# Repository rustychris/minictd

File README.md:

# minictd
Hardware and firmware for miniature, low-fi CTD

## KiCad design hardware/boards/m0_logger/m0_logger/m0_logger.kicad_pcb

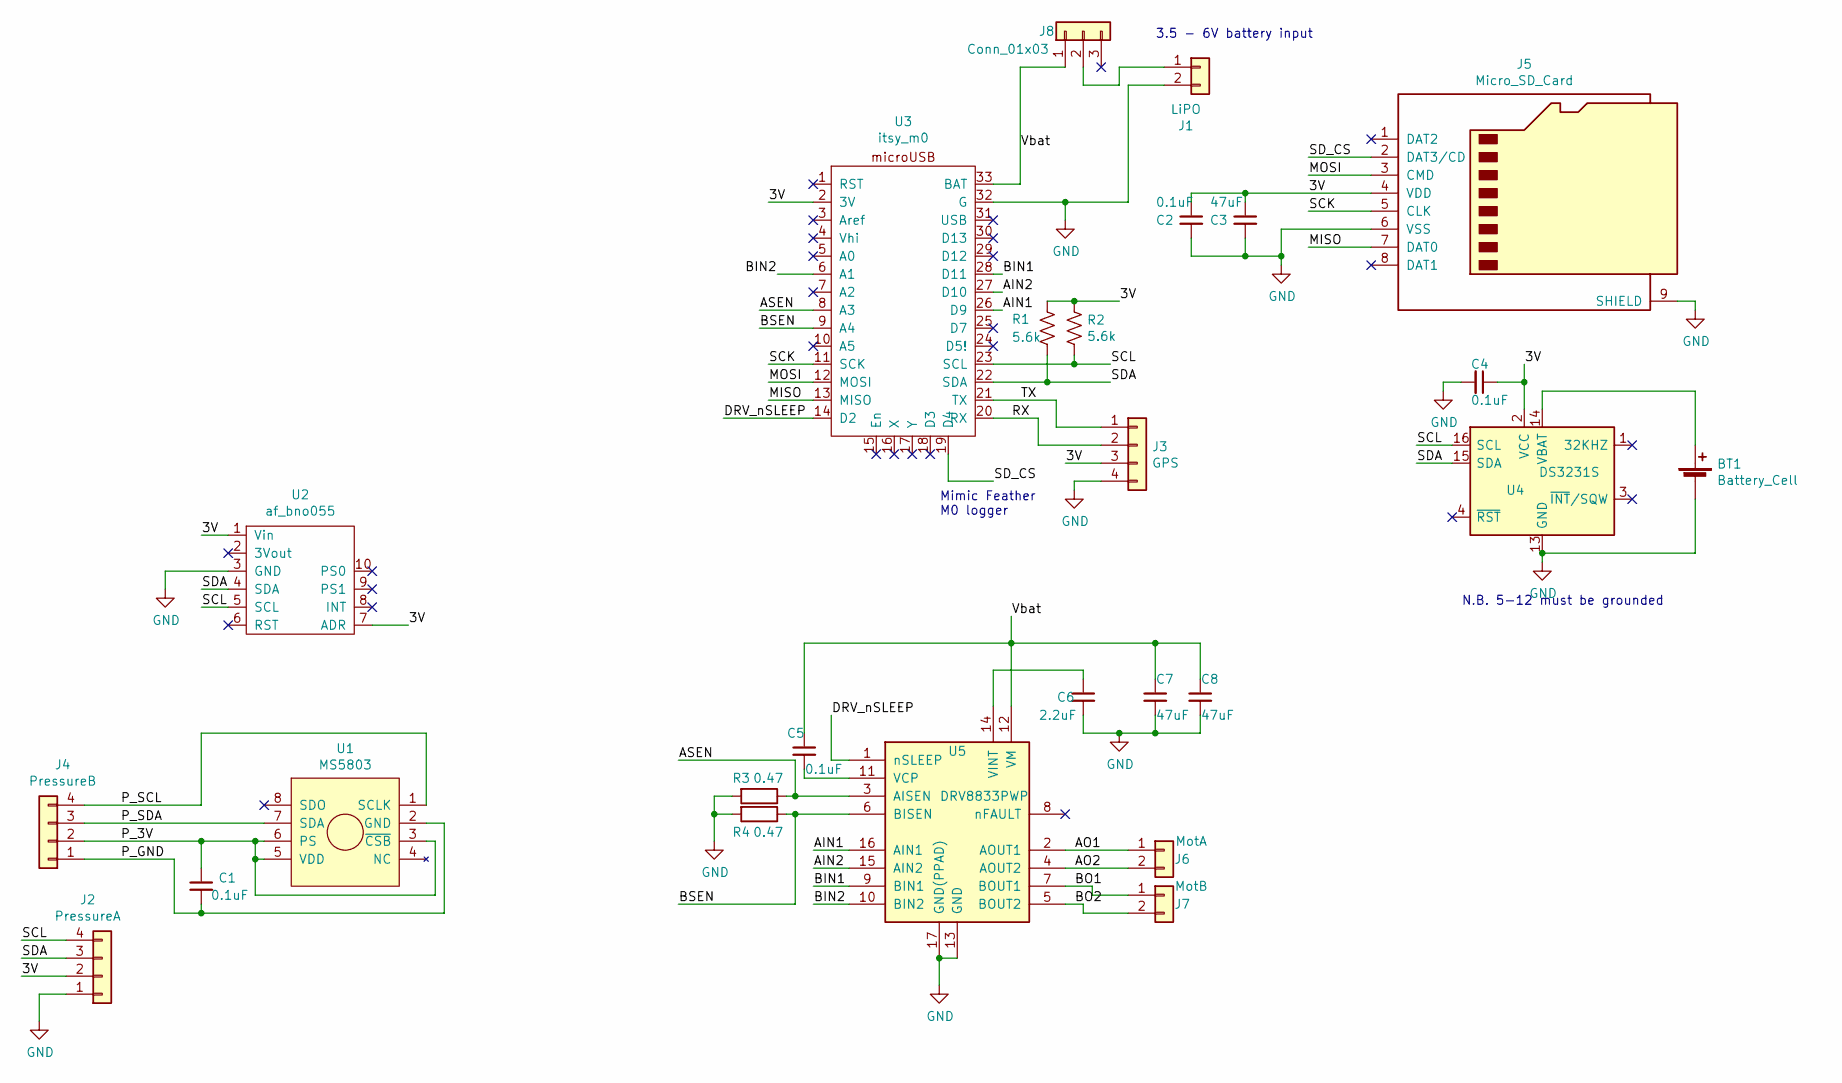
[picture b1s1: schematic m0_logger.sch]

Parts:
BT1: Battery_Cell; BatteryHolder_Keystone_500
C1, C2, C4, C5: 0.1uF; C_0805_2012Metric_Pad1.15x1.40mm_HandSolder
C3, C7, C8: 47uF; C_0805_2012Metric_Pad1.15x1.40mm_HandSolder
C6: 2.2uF; C_0805_2012Metric_Pad1.15x1.40mm_HandSolder
J1: LiPO; JST_PH_S2B-PH-K_1x02_P2.00mm_Horizontal
J2: PressureA; Molex_PicoBlade_53047-0810_1x04_P1.25mm_Vertical
J3: GPS; Molex_PicoBlade_53047-0810_1x04_P1.25mm_Vertical
J4: PressureB; PinHeader_1x04_P2.54mm_Vertical
J5: Micro_SD_Card; microSD_HC_Hirose_DM3AT-SF-PEJM5
J6: MotA; Molex_PicoBlade_53047-0410_1x02_P1.25mm_Vertical
J7: MotB; Molex_PicoBlade_53047-0410_1x02_P1.25mm_Vertical
J8: Conn_01x03; PinHeader_1x03_P2.54mm_Vertical
R1, R2: 5.6k; R_0805_2012Metric_Pad1.15x1.40mm_HandSolder
R3, R4: 0.47; R_0805_2012Metric_Pad1.15x1.40mm_HandSolder
U1: MS5803; ms5803_rh
U2: af_bno055; afBNO055
U3: itsy_m0; ItsyBitsyM0
U4: DS3231S; SOIC-16W_7.5x10.3mm_P1.27mm
U5: DRV8833PWP; HTSSOP-16-1EP_4.4x5mm_P0.65mm_EP3.4x5mm_Mask2.46x2.31mm_The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

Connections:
/3V: C2.1, C3.1, C4.1, J2.2, J3.3, J5.4 (VDD), R1.1, R2.1, U2.1 (Vin), U2.7 (ADR), U3.2 (3V), U4.2 (VCC)
/AIN1: U3.26 (D9), U5.16 (AIN1)
/AIN2: U3.27 (D10), U5.15 (AIN2)
/AO1: J6.1, U5.2 (AOUT1)
/AO2: J6.2, U5.4 (AOUT2)
/ASEN: R3.1, U3.8 (A3), U5.3 (AISEN)
/BIN1: U3.28 (D11), U5.9 (BIN1)
/BIN2: U3.6 (A1), U5.10 (BIN2)
/BO1: J7.1, U5.7 (BOUT1)
/BO2: J7.2, U5.5 (BOUT2)
/BSEN: R4.1, U3.9 (A4), U5.6 (BISEN)
/DRV_nSLEEP: U3.14 (D2), U5.1 (nSLEEP)
/MISO: J5.7 (DAT0), U3.13 (MISO)
/MOSI: J5.3 (CMD), U3.12 (MOSI)
/P_3V: C1.1, J4.2, U1.3 (~CSB~), U1.5 (VDD), U1.6 (PS); also elsewhere on the board
/P_GND: C1.2, J4.1, U1.2 (GND); also elsewhere on the board
/P_SCL: J4.4, U1.1 (SCLK); also elsewhere on the board
/P_SDA: J4.3, U1.7 (SDA); also elsewhere on the board
/RX: J3.2, U3.20 (RX)
/SCK: J5.5 (CLK), U3.11 (SCK)
/SCL: J2.4, R2.2, U2.5 (SCL), U3.23 (SCL), U4.16 (SCL)
/SDA: J2.3, R1.2, U2.4 (SDA), U3.22 (SDA), U4.15 (SDA)
/SD_CS: J5.2 (DAT3/CD), U3.19 (D4)
/TX: J3.1, U3.21 (TX)
/Vbat: C5.1, C7.1, C8.1, J8.1, U3.33 (BAT), U5.12 (VM)
GND: BT1.2 (-), C2.2, C3.2, C4.2, C6.2, C7.2, C8.2, J1.2, J2.1, J3.4, J5.6 (VSS), J5.9 (SHIELD), R3.2, R4.2, U2.3 (GND), U3.32 (G), U4.5 (GND), U4.6 (GND), U4.7 (GND), U4.8 (GND), U4.9 (GND), U4.10 (GND), U4.11 (GND), U4.12 (GND), U4.13 (GND), U5.13 (GND), U5.17 (GND(PPAD))
unnamed: BT1.1 (+), U4.14 (VBAT)
unnamed: C5.2, U5.11 (VCP)
unnamed: C6.1, U5.14 (VINT)
unnamed: J1.1, J8.2

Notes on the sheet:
N.B. 5-12 must be grounded
Mimic Feather M0 logger
3.5 - 6V battery input

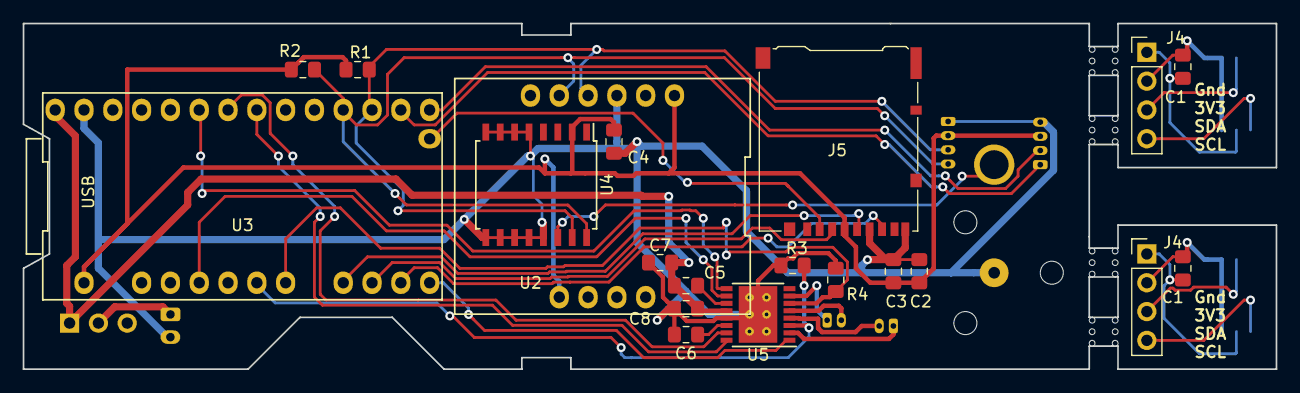
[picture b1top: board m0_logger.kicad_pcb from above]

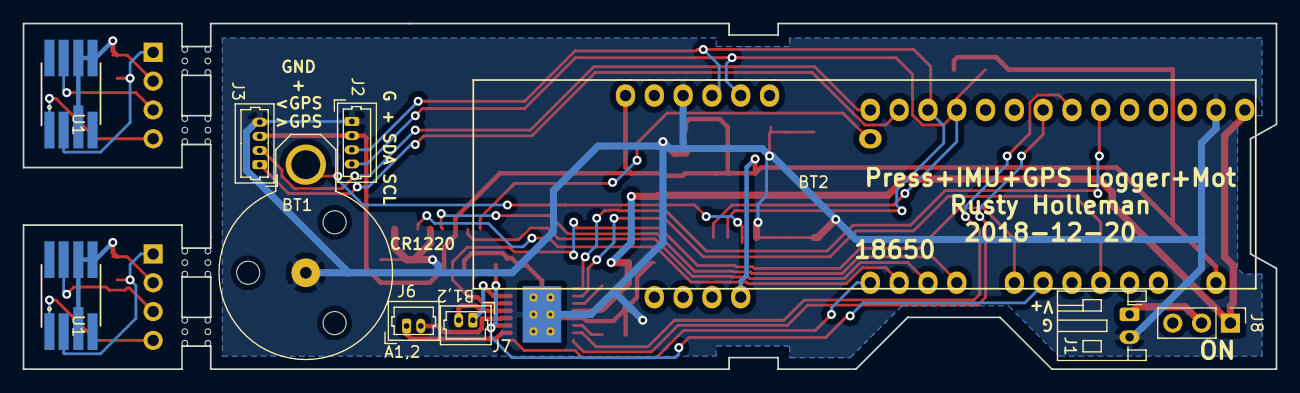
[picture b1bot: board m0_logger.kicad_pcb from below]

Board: 2 copper layers, 110.5 x 30.5 mm, 30 parts (10 on the bottom side), 30 nets.

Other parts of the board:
BT2: 18650, protected; af18650_outline
C1#2: 0.1uF; C_0805_2012Metric_Pad1.15x1.40mm_HandSolder
J4#2: PressureB; PinHeader_1x04_P2.54mm_Vertical
U1#2: MS5803; ms5803_rh

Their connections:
/P_3V: C1#2.1, J4#2.2, U1#2.3, U1#2.5, U1#2.6; also elsewhere on the board
/P_GND: C1#2.2, J4#2.1, U1#2.2; also elsewhere on the board
/P_SCL: J4#2.4, U1#2.1; also elsewhere on the board
/P_SDA: J4#2.3, U1#2.7; also elsewhere on the board

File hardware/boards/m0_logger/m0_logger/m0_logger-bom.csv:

"Ref","Qnty","Value","Cmp name","Footprint","Description","Vendor"
"BT1, ","1","Battery_Cell","Battery_Cell","Battery:BatteryHolder_Keystone_500","Single-cell battery","36-500-ND"
"C1, C4, C2, ","3","0.1uF","C_Small","Capacitor_SMD:C_0805_2012Metric_Pad1.15x1.40mm_HandSolder","Unpolarized capacitor, small symbol","478-1395-1-ND"
"C3, ","1","47uF","C_Small","Capacitor_SMD:C_0805_2012Metric_Pad1.15x1.40mm_HandSolder","Unpolarized capacitor, small symbol","490-9961-1-ND"
"J1, ","1","LiPO","Conn_01x02","Connector_JST:JST_PH_S2B-PH-K_1x02_P2.00mm_Horizontal","Generic connector, single row, 01x02, script generated (kicad-library-utils/schlib/autogen/connector/)","455-1719-ND"
"J2, ","1","PressureA","Conn_01x04","Connector_PinHeader_2.54mm:PinHeader_2x02_P2.54mm_Horizontal","Generic connector, single row, 01x04, script generated (kicad-library-utils/schlib/autogen/connector/)","609-3333-ND"
"J3, ","1","GPS","Conn_01x04","Connector_PinHeader_2.54mm:PinHeader_2x02_P2.54mm_Horizontal","Generic connector, single row, 01x04, script generated (kicad-library-utils/schlib/autogen/connector/)","609-3333-ND"
"J4, ","1","PressureB","Conn_01x04","Connector_PinHeader_2.54mm:PinHeader_1x04_P2.54mm_Vertical","Generic connector, single row, 01x04, script generated (kicad-library-utils/schlib/autogen/connector/)","609-3255-ND"
"J5, ","1","Micro_SD_Card","Micro_SD_Card","Connector_Card:microSD_HC_Hirose_DM3AT-SF-PEJM5","Micro SD Card Socket","HR1964CT-ND"
"R2, R1, ","2","5.6k","R_US","Resistor_SMD:R_0805_2012Metric_Pad1.15x1.40mm_HandSolder","Resistor, US symbol","A126380CT-ND"
"U1, ","1","MS5803","MS5803","m0_logger_footprints:ms5803_rh","","223-1625-5-ND"
"U2, ","1","af_bno055","af_bno055","m0_logger_footprints:afBNO055","","1528-1426-ND"
"U3, ","1","itsy_m0","itsy_m0","m0_logger_footprints:ItsyBitsyM0","","1528-2554-ND"
"U4, ","1","DS3231S","DS3231M","Package_SO:SOIC-16W_7.5x10.3mm_P1.27mm","Extremely Accurate I2C-Integrated RTC/TCXO/Crystal SOIC-16","DS3231S#-ND"

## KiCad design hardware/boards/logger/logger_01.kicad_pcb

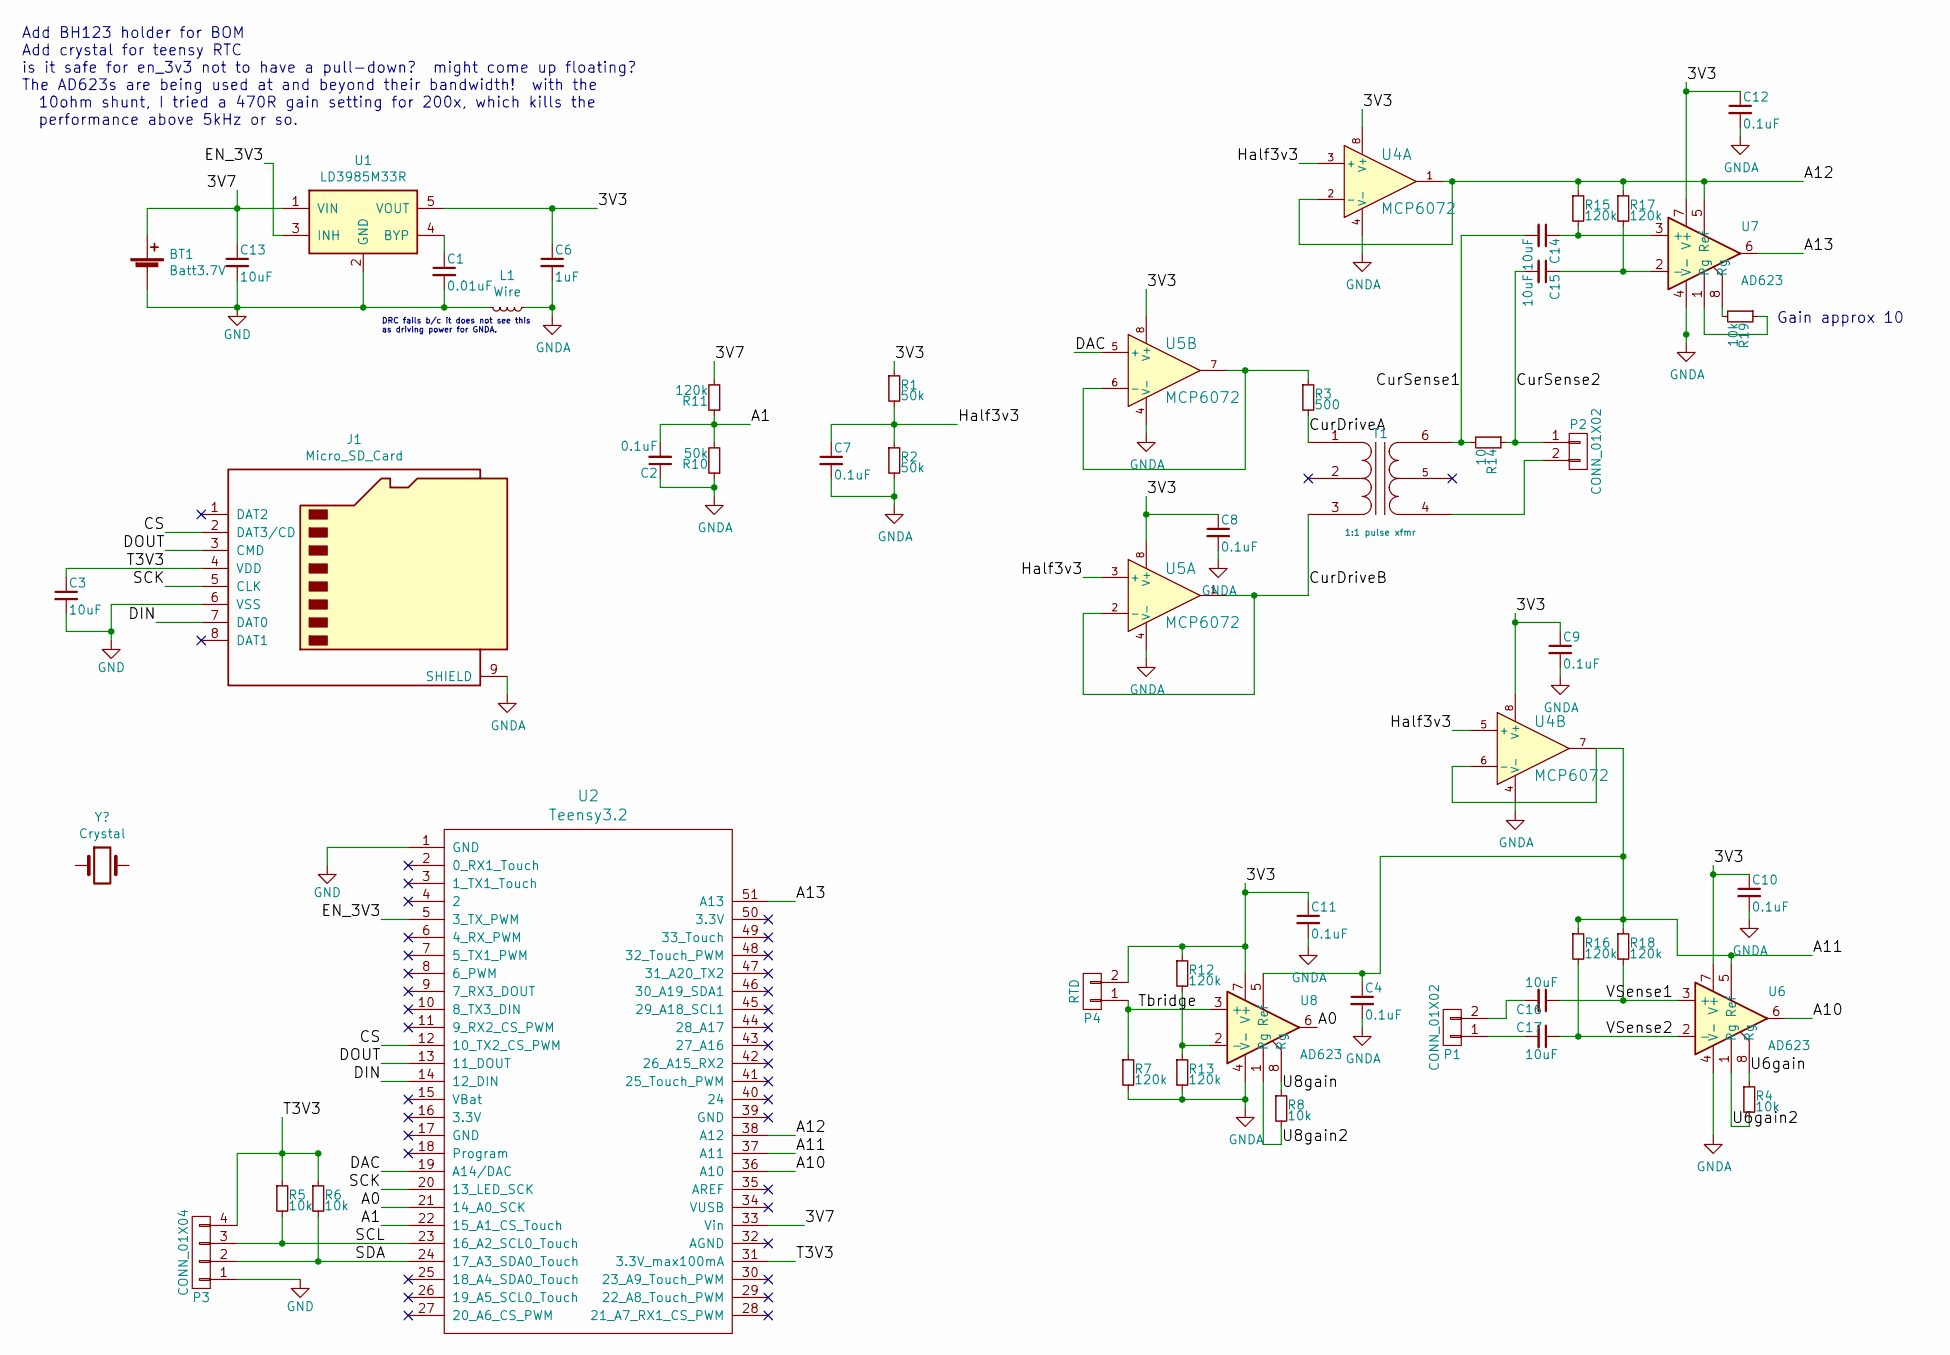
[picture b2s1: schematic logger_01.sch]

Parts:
BT1: Batt3.7V; Pin_Header_Straight_1x02_Pitch2.54mm
C1: 0.01uF; C_0805_HandSoldering; part_num CC0805KRX7R9BB103; digikey_num 311-1136-1-ND
C2, C7: 0.1uF; C_0805_HandSoldering; part_num 08055C104KAT2A; digikey_num 478-1395-1-ND
C3, C13, C14, C15, C16, C17: 10uF; C_0805_HandSoldering; part_num GRM21BR61E106KA73L; digikey_num 490-5523-1-ND
C4, C8, C9, C10, C11, C12: 0.1uF; C_0805_HandSoldering; part_num 08055C104KAT2A
C6: 1uF; C_0805_HandSoldering; part_num GRM21BR61E106KA73L; digikey_num 490-5523-1-ND
J1: Micro_SD_Card; molex5031821852; part_num 5031821852; digikey_num WM12834CT-ND
L1: Wire; R_0805
P1, P2: CONN_01X02; Pin_Header_Straight_1x02_Pitch2.54mm
P3: CONN_01X04; Pin_Header_Straight_1x04_Pitch2.54mm; part_num S1011EC-12-ND; digikey_num PRPC012SAAN-RC
P4: RTD; Pin_Header_Straight_1x02_Pitch2.54mm
R1, R2, R10: 50k; R_0805_HandSoldering; part_num RT0805DRE0722K1L; digikey_num 311-2825-1-ND
R3: 500; R_0805_HandSoldering; part_num RR1220P-471-D; digikey_num RR12P470DCT-ND
R4, R6, R8, R19: 10k; R_0805_HandSoldering; part_num RT0805DRD0712K1L
R5: 10k; R_0805_HandSoldering; part_num RT0805DRD0712K1L; digikey_num 311-2703-1-ND
R7, R12, R13, R15, R16, R17, R18: 120k; R_0805_HandSoldering; part_num RT0805DRD07120KL; digikey_num 311-2702-1-ND
R11: 120k; R_0805_HandSoldering; part_num RT0805DRE0722K1L; digikey_num 311-2825-1-ND
R14: 10; R_0805_HandSoldering; part_num RT0805DRD0710RL; digikey_num 311-2700-1-ND
T1: 1:1 pulse xfmr; 6pin_pulse_transformer; part_num 78253/55JC; digikey_num 811-2415-ND
U1: LD3985M33R; SOT-23-5; part_num LD3985M33R; digikey_num 497-3504-1-ND
U2: Teensy3.2; Teensy32_for_logger
U4: MCP6072; SOIC-8_3.9x4.9mm_Pitch1.27mm; part_num MCP6072-E/SN; digikey MCP6072-E/SN-ND
U5: MCP6072; SOIC-8_3.9x4.9mm_Pitch1.27mm; part_num MCP6072-E/SN; digikey_num MCP6072-E/SN-ND
U6, U7, U8: AD623; SOIC-8_3.9x4.9mm_Pitch1.27mm; part_num AD623ARZ; digikey_num AD623ARZ-ND

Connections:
/3V3: C6.1, C8.1, C9.1, C10.1, C11.1, C12.1, P4.2, R1.1, R12.1, U1.5 (VOUT), U4.8 (V+), U5.8 (V+), U6.7 (V+), U7.7 (V+), U8.7 (V+)
/3V7: BT1.1 (+), C13.1, R11.2, U1.1 (VIN), U2.33 (Vin)
/A0: U2.21 (14_A0_SCK), U8.6
/A1: C2.2, R10.2, R11.1, U2.22 (15_A1_CS_Touch)
/A10: U2.36 (A10), U6.6
/A11: C4.1, R16.1, R18.1, U2.37 (A11), U4.6 (-), U4.7, U6.5 (Ref), U8.5 (Ref)
/A12: R15.1, R17.1, U2.38 (A12), U4.1, U4.2 (-), U7.5 (Ref)
/A13: U2.51 (A13), U7.6
/CS: J1.2 (DAT3/CD), U2.12 (10_TX2_CS_PWM)
/CurDriveA: R3.2, T1.1 (PR1)
/CurDriveB: T1.3 (PR2), U5.1, U5.2 (-)
/CurSense1: C14.2, R14.2, T1.6 (S2)
/CurSense2: C15.2, P2.1, R14.1
/DAC: U2.19 (A14/DAC), U5.5 (+)
/DIN: J1.7 (DAT0), U2.14 (12_DIN)
/DOUT: J1.3 (CMD), U2.13 (11_DOUT)
/EN_3V3: U1.3 (INH), U2.5 (3_TX_PWM)
/Half3v3: C7.1, R1.2, R2.1, U4.3 (+), U4.5 (+), U5.3 (+)
/SCK: J1.5 (CLK), U2.20 (13_LED_SCK)
/SCL: P3.3, R5.2, U2.23 (16_A2_SCL0_Touch)
/SDA: P3.2, R6.2, U2.24 (17_A3_SDA0_Touch)
/T3V3: C3.1, J1.4 (VDD), P3.4, R5.1, R6.1, U2.31 (3.3V_max100mA)
/Tbridge: P4.1, R7.1, U8.3 (+)
/U6gain: R4.1, U6.8 (Rg)
/U6gain2: R4.2, U6.1 (Rg)
/U8gain: R8.1, U8.8 (Rg)
/U8gain2: R8.2, U8.1 (Rg)
/VSense1: C16.1, R18.2, U6.3 (+)
/VSense2: C17.1, R16.2, U6.2 (-)
GND: BT1.2 (-), C1.2, C3.2, C13.2, J1.6 (VSS), L1.2, P3.1, U1.2 (GND), U2.1 (GND); also elsewhere on the board
GNDA: C2.1, C4.2, C6.2, C7.2, C8.2, C9.2, C10.2, C11.2, C12.2, J1.9 (SHIELD), L1.1, R2.2, R7.2, R10.1, R13.2, U4.4 (V-), U5.4 (V-), U6.4 (V-), U7.4 (V-), U8.4 (V-); also elsewhere on the board
unnamed: C1.1, U1.4 (BYP)
unnamed: C14.1, R15.2, U7.3 (+)
unnamed: C15.1, R17.2, U7.2 (-)
unnamed: C16.2, P1.2
unnamed: C17.2, P1.1
unnamed: P2.2, T1.4 (S1)
unnamed: R3.1, U5.6 (-), U5.7
unnamed: R12.2, R13.1, U8.2 (-)
unnamed: R19.1, U7.1 (Rg)
unnamed: R19.2, U7.8 (Rg)

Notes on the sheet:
Gain approx 10
DRC fails b/c it does not see this as driving power for GNDA.
Add BH123 holder for BOM Add crystal for teensy RTC is it safe for en_3v3 not to have a pull-down? might come up floating? The AD623s are being used at and beyond their bandwidth! with the 10ohm shunt, I tried a 470R gain setting for 200x, which kills the performance above 5kHz or so.

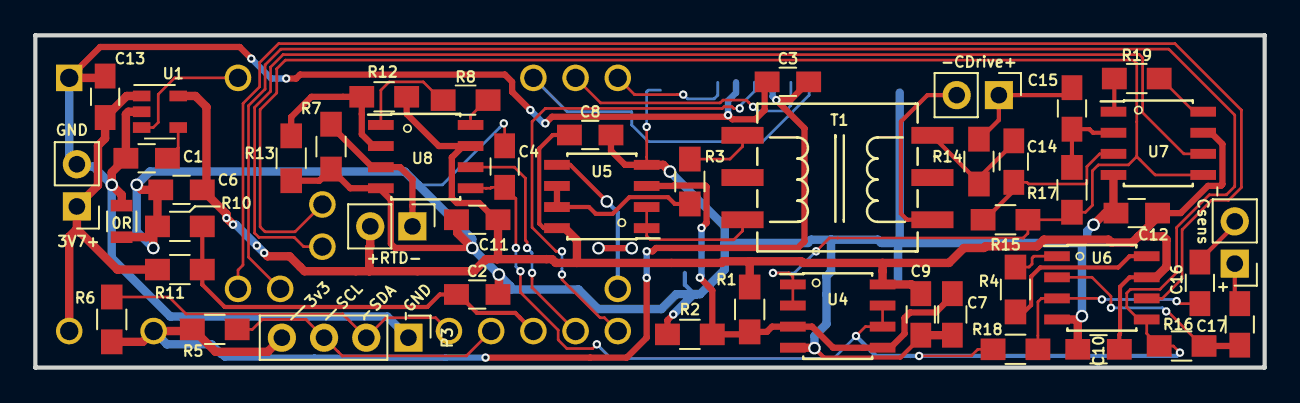
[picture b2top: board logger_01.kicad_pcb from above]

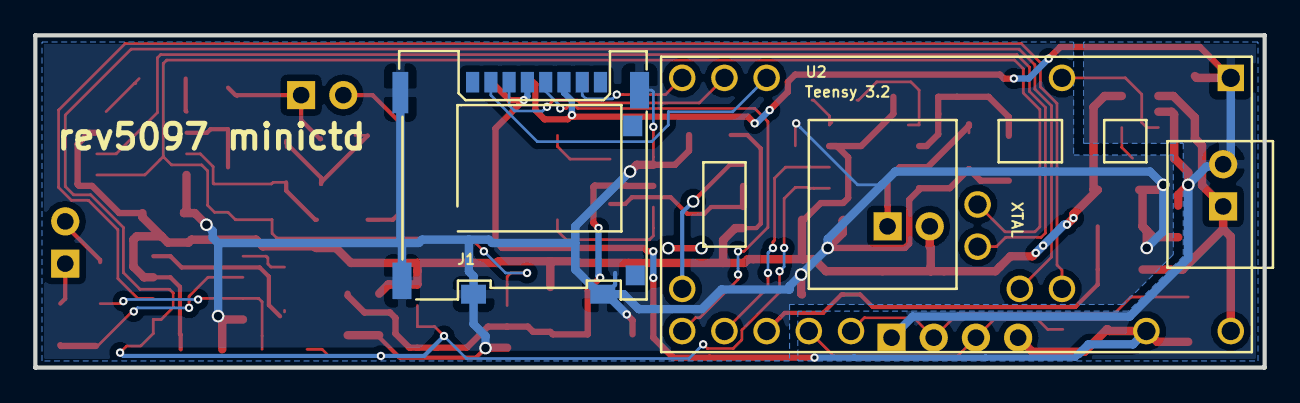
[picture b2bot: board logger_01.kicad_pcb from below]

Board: 2 copper layers, 74.0 x 20.0 mm, 49 parts (2 on the bottom side), 41 nets.

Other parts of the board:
0R: Wire; R_0805

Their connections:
GND: 0R.2; also elsewhere on the board
GNDA: 0R.1; also elsewhere on the board

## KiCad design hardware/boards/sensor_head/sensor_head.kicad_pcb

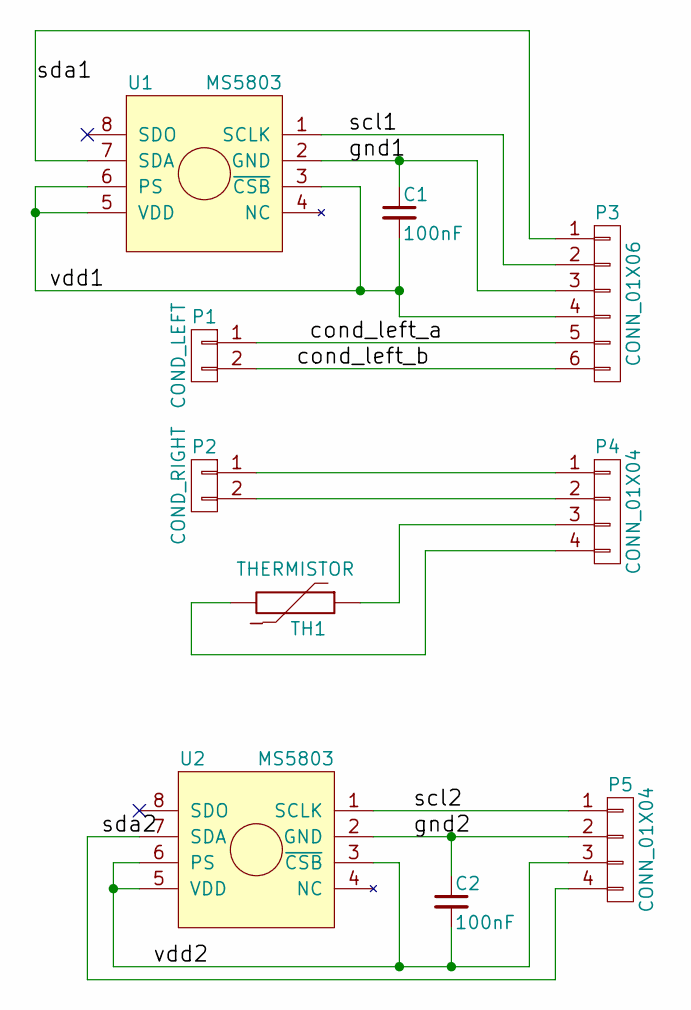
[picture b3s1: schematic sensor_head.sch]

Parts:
C1, C2: 100nF; C_Disc_D6_P5
P1: COND_LEFT; cond_10mm
P2: COND_RIGHT; cond_10mm
P3: CONN_01X06; Pin_Header_Straight_1x06
P4, P5: CONN_01X04; Pin_Header_Straight_1x04
TH1: THERMISTOR; R1
U1: MS5803; MS5803-through
U2: MS5803; ms5803-surface

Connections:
/cond_left_a: P1.1, P3.5
/cond_left_b: P1.2, P3.6
/gnd1: C1.1, P3.3, U1.2 (GND)
/gnd2: C2.1, P5.2, U2.2 (GND)
/scl1: P3.2, U1.1 (SCLK)
/scl2: P5.1, U2.1 (SCLK)
/sda1: P3.1, U1.7 (SDA)
/sda2: P5.4, U2.7 (SDA)
/vdd1: C1.2, P3.4, U1.3 (~CSB~), U1.5 (VDD), U1.6 (PS)
/vdd2: C2.2, P5.3, U2.3 (~CSB~), U2.5 (VDD), U2.6 (PS)
unnamed: P2.1, P4.1
unnamed: P2.2, P4.2
unnamed: P4.3, TH1.1
unnamed: P4.4, TH1.2

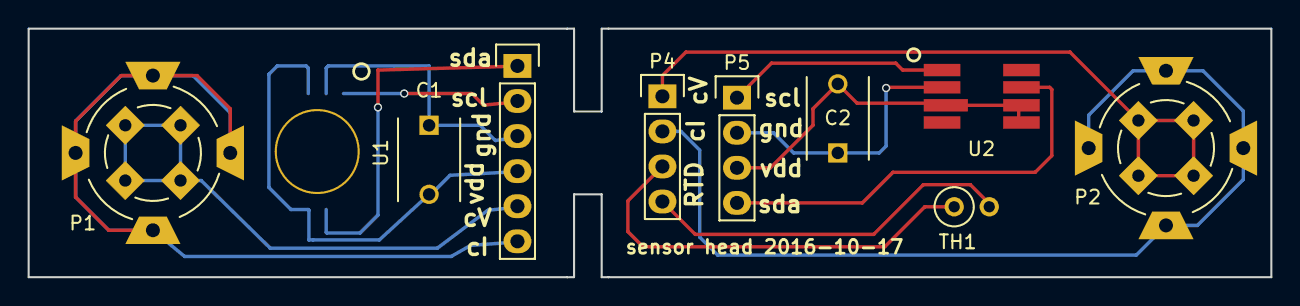
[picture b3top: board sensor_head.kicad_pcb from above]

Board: 2 copper layers, 90.0 x 18.0 mm, 10 parts (0 on the bottom side), 14 nets.

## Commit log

2017-06-13 initial import
2017-07-04 Update layout with info for fabrication, notes for next rev
2017-07-04 add teensyduino code to repo
2017-07-04 adding pcb for sensor head
2017-07-04 minor pcb doc changes
2017-07-04 get new project to compile after move
2017-07-07 new notes
2017-08-03 Long overdue update.
2017-08-27 Complete refactor, minor testing, add RTC.
2017-08-29 Bring in SdFat library
2017-09-20 Fixed pin config for pressure, SD card.
    Can read pressure, SD card, thermistor, cond. cell.
2017-12-06 Add binary streaming, other fixes and refactors
2017-12-23 Refactor Sensor, new commands.
2018-01-01 Refactor, ready to make sampling async
2018-01-01 Last bit of that update
2018-01-02 Start on async transition for pressure.
2018-01-04 Working async pressure.
2018-01-05 Add async testing for conductivity
    Compiles, but untested.
2018-01-06 Make temperaure async
2018-01-07 Transition to asynchronous sampling.
2018-01-07 Enable logging to SD.
2018-01-08 Enable SD command file
2018-10-11 many adaptations to feather board
2018-10-13 compile for zero
2018-10-14 Basic boot now working.
    Successfully reads pressure, SD card, fake RTC.
2018-10-30 Add IMU support, BNO055
2018-11-01 non-working async i2c
2018-11-01 Async i2c working via DMAC
2018-11-02 Transition back to standard I2C pins
2018-11-02 Refactoring and using standard i2c
2018-11-03 Basic IMU working
2018-11-08 Clock basically working.
2018-11-08 Fix timer conflict, add green led while sampling
2018-11-13 optionally go headless
2018-11-28 GPS, pcb layout
2018-11-28 tweaks
2018-12-10 PCB layout sent, minor CAD for housing
2018-12-18 Start layout of next board revision
2018-12-19 Finish layout for 2nd revision
2018-12-20 rev2 submitted
2019-01-20 Initial motor code, successfully tested.
2019-01-29 Test RTC, imu, fix some documentation and missing commands.
    All aspects of board check out.
2019-02-25 Tweaks while testing new boards
2019-03-06 Towards buoyancy control
2019-03-06 starting point for buoyancy control
2019-03-08 Working bluetooh and buoyancy control.
2019-03-11 GPS logging fix to remove null bytes
2019-03-14 Simulation code for buoyancy, config for buoyancy
2019-03-14 Fix gravity term, and switch to canned integration
2019-03-15 change of control variable
2019-03-16 Tweaks to get off the surface
2019-03-21 Update PID Controller to command piston volume.
    Previously PID controller commanded motor on/off.
2019-03-22 Fix cruft at start of files. Also more PID output
2019-03-24 More debug messages, avoid resetting motor position, and force neutral between fwd and rev.
2019-03-26 Non-functional zmodem implementation
2019-04-04 Add XModem file transfer, and BT AT mode support
2019-04-10 Add yoyo command, and refactor to allow reentrant commands.
    Allow for compound commands which can call parse to execute
    sub-commands.
2019-04-10 Add dates and decimal seconds to parsing, 1k xmodem/ymodem.
2020-03-24 progress on samd21 dac-adc loop
2020-08-01 Old changes for buoyancy engine
2020-08-01 Basic working inductive sense
2020-08-01 RTD test code
2020-08-01 Old edits, forgot to commit
